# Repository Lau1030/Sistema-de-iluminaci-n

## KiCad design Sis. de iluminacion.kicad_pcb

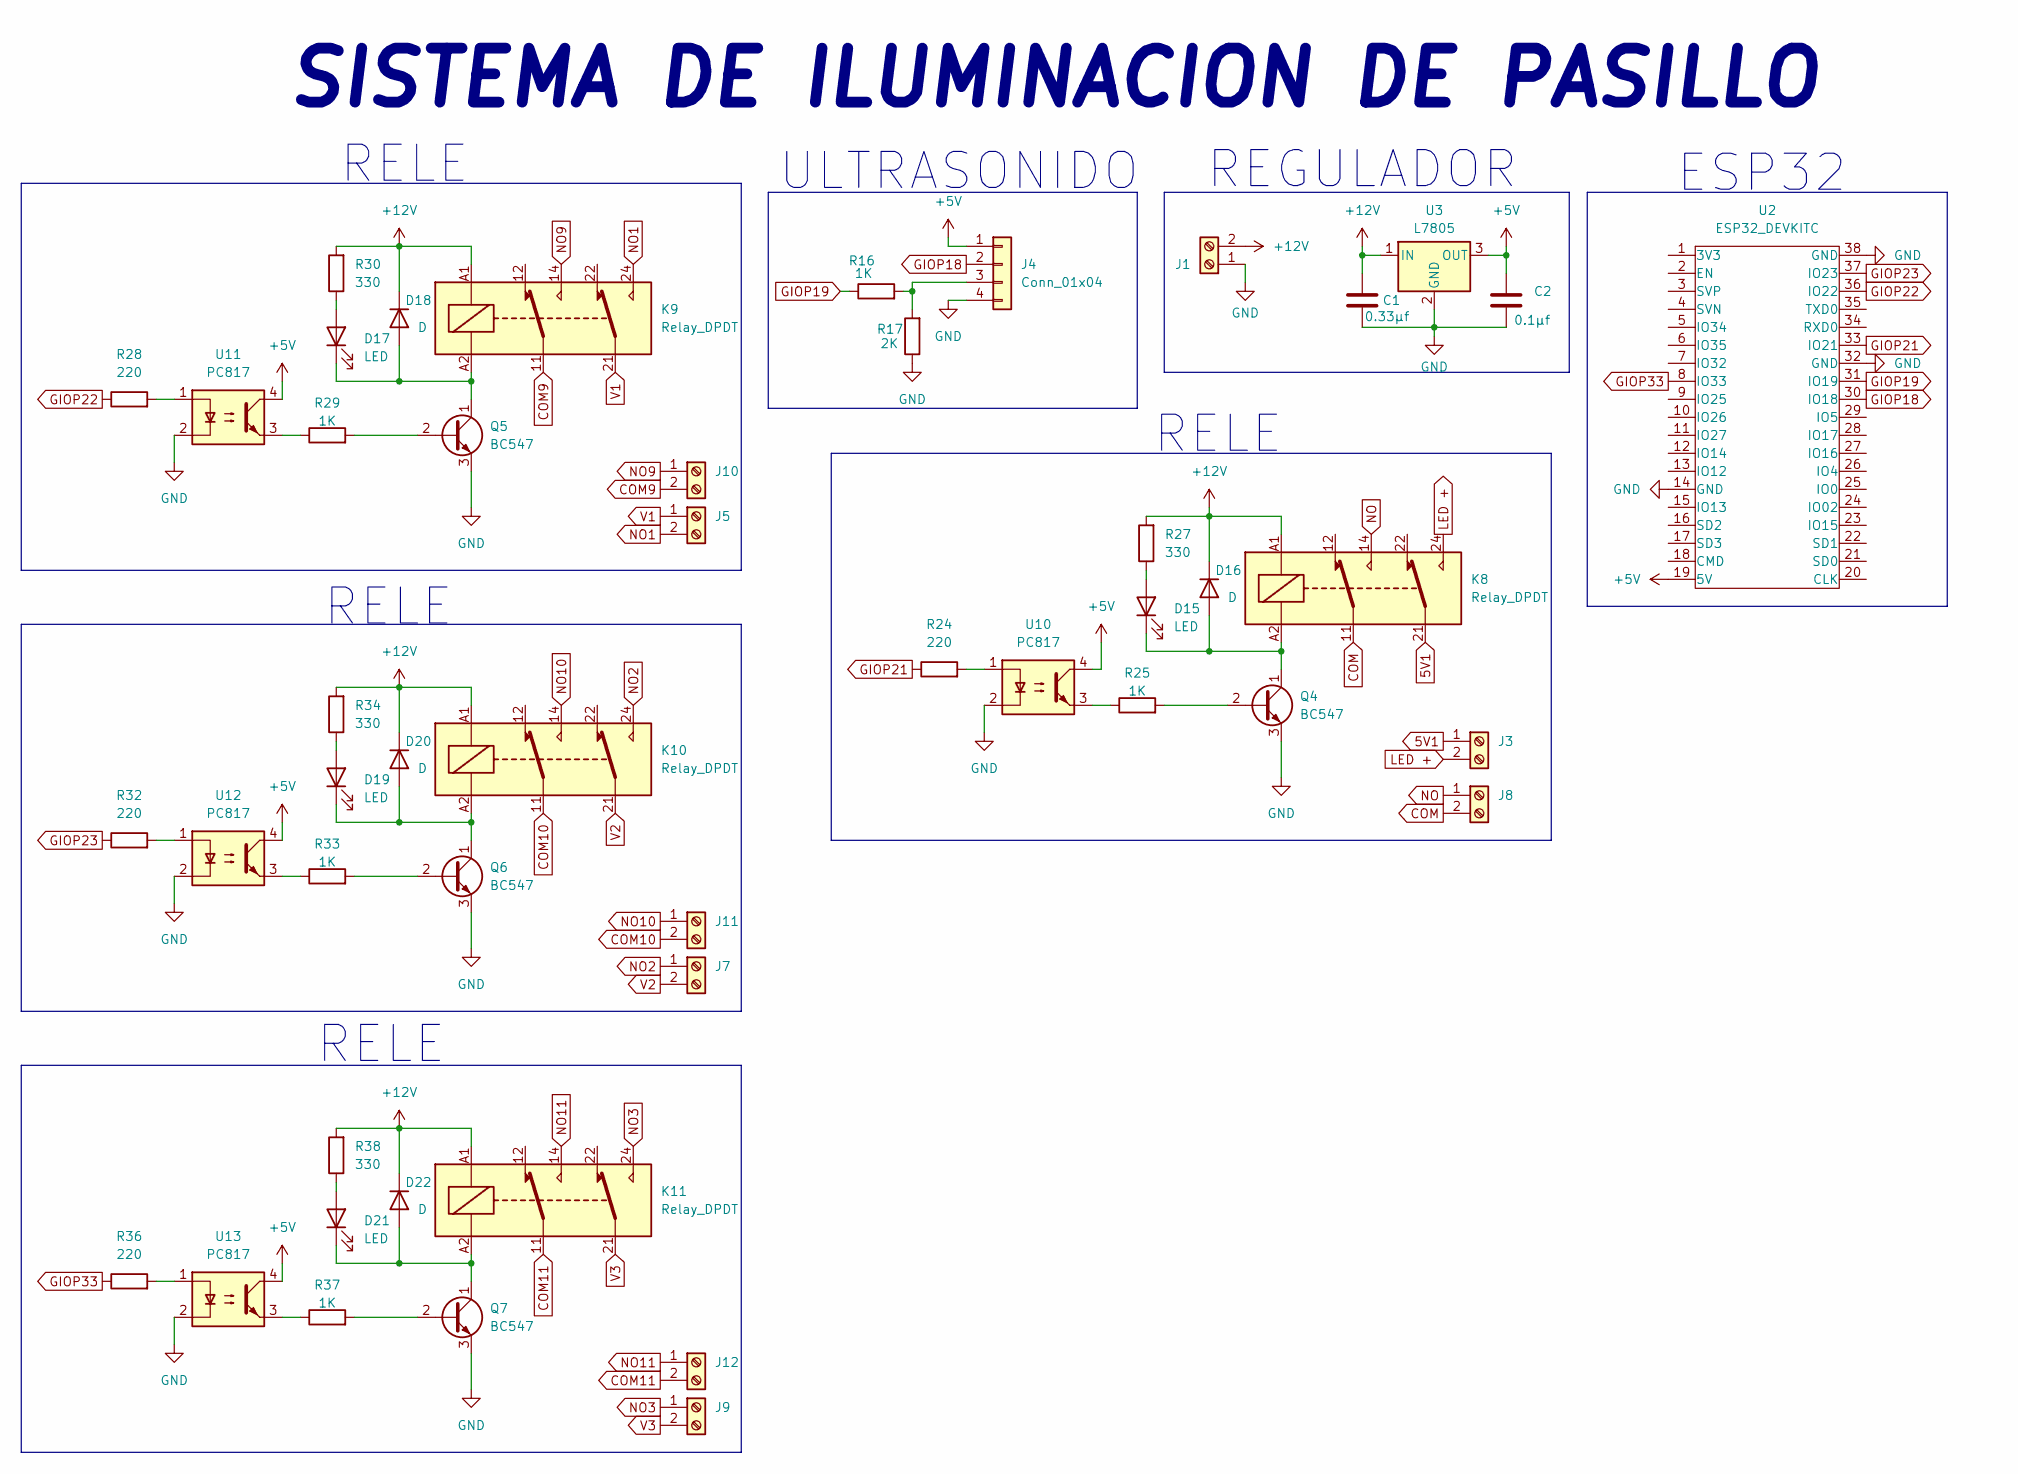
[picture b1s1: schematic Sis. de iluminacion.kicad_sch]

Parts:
C1: 0.33µf; C_0805_2012Metric
C2: 0.1µf; C_0805_2012Metric
D15, D17, D19, D21: LED; LED_0805_2012Metric
D16, D18, D20, D22: D; D_SMA
J1, J3, J5, J7, J8, J9, J10, J11, J12: Screw_Terminal_01x02; TerminalBlock_MaiXu_MX126-5.0-02P_1x02_P5.00mm
J4: Conn_01x04; PinSocket_1x04_P2.54mm_Vertical
K8, K9, K10, K11: Relay_DPDT; Relay_DPDT_Omron_G6A
Q4, Q5, Q6, Q7: BC547; TO-92_Wide
R16, R25, R29, R33, R37: 1K; R_0805_2012Metric
R17: 2K; R_0805_2012Metric
R24, R28, R32, R36: 220; R_0805_2012Metric
R27, R30, R34, R38: 330; R_0805_2012Metric
U2: ESP32_DEVKITC; ESP32S
U3: L7805; TO-263-3_TabPin2
U10, U11, U12, U13: PC817; DIP-4_W7.62mm

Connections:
5V1: J3.1, K8.21
+5V: C2.1, J4.1, U2.19 (5V), U3.3 (OUT), U10.4, U11.4, U12.4, U13.4
+12V: C1.1, D16.1 (K), D18.1 (K), D20.1 (K), D22.1 (K), J1.2, K8.A1, K9.A1, K10.A1, K11.A1, R27.2, R30.2, R34.2, R38.2, U3.1 (IN)
COM: J8.2, K8.11
COM9: J10.2, K9.11
COM10: J11.2, K10.11
COM11: J12.2, K11.11
GIOP18: J4.2, U2.30 (IO18)
GIOP19: R16.1, U2.31 (IO19)
GIOP21: R24.1, U2.33 (IO21)
GIOP22: R28.1, U2.36 (IO22)
GIOP23: R32.1, U2.37 (IO23)
GIOP33: R36.1, U2.8 (IO33)
GND: C1.2, C2.2, J1.1, J4.4, Q4.3 (E), Q5.3 (E), Q6.3 (E), Q7.3 (E), R17.1, U2.14 (GND), U2.32 (GND), U2.38 (GND), U3.2 (GND), U10.2, U11.2, U12.2, U13.2
LED +: J3.2, K8.24
NO: J8.1, K8.14
NO1: J5.2, K9.24
NO2: J7.1, K10.24
NO3: J9.1, K11.24
NO9: J10.1, K9.14
NO10: J11.1, K10.14
NO11: J12.1, K11.14
unnamed: D15.2 (A), R27.1
unnamed: D15.1 (K), D16.2 (A), K8.A2, Q4.1 (C)
unnamed: D17.2 (A), R30.1
unnamed: D17.1 (K), D18.2 (A), K9.A2, Q5.1 (C)
unnamed: D19.2 (A), R34.1
unnamed: D19.1 (K), D20.2 (A), K10.A2, Q6.1 (C)
unnamed: D21.2 (A), R38.1
unnamed: D21.1 (K), D22.2 (A), K11.A2, Q7.1 (C)
unnamed: J4.3, R16.2, R17.2
unnamed: Q4.2 (B), R25.2
unnamed: Q5.2 (B), R29.2
unnamed: Q6.2 (B), R33.2
unnamed: Q7.2 (B), R37.2
unnamed: R24.2, U10.1
unnamed: R25.1, U10.3
unnamed: R28.2, U11.1
unnamed: R29.1, U11.3
unnamed: R32.2, U12.1
unnamed: R33.1, U12.3
unnamed: R36.2, U13.1
unnamed: R37.1, U13.3
V1: J5.1, K9.21
V2: J7.2, K10.21
V3: J9.2, K11.21

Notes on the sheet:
RELE
SISTEMA DE ILUMINACION DE PASILLO
ULTRASONIDO
REGULADOR
ESP32

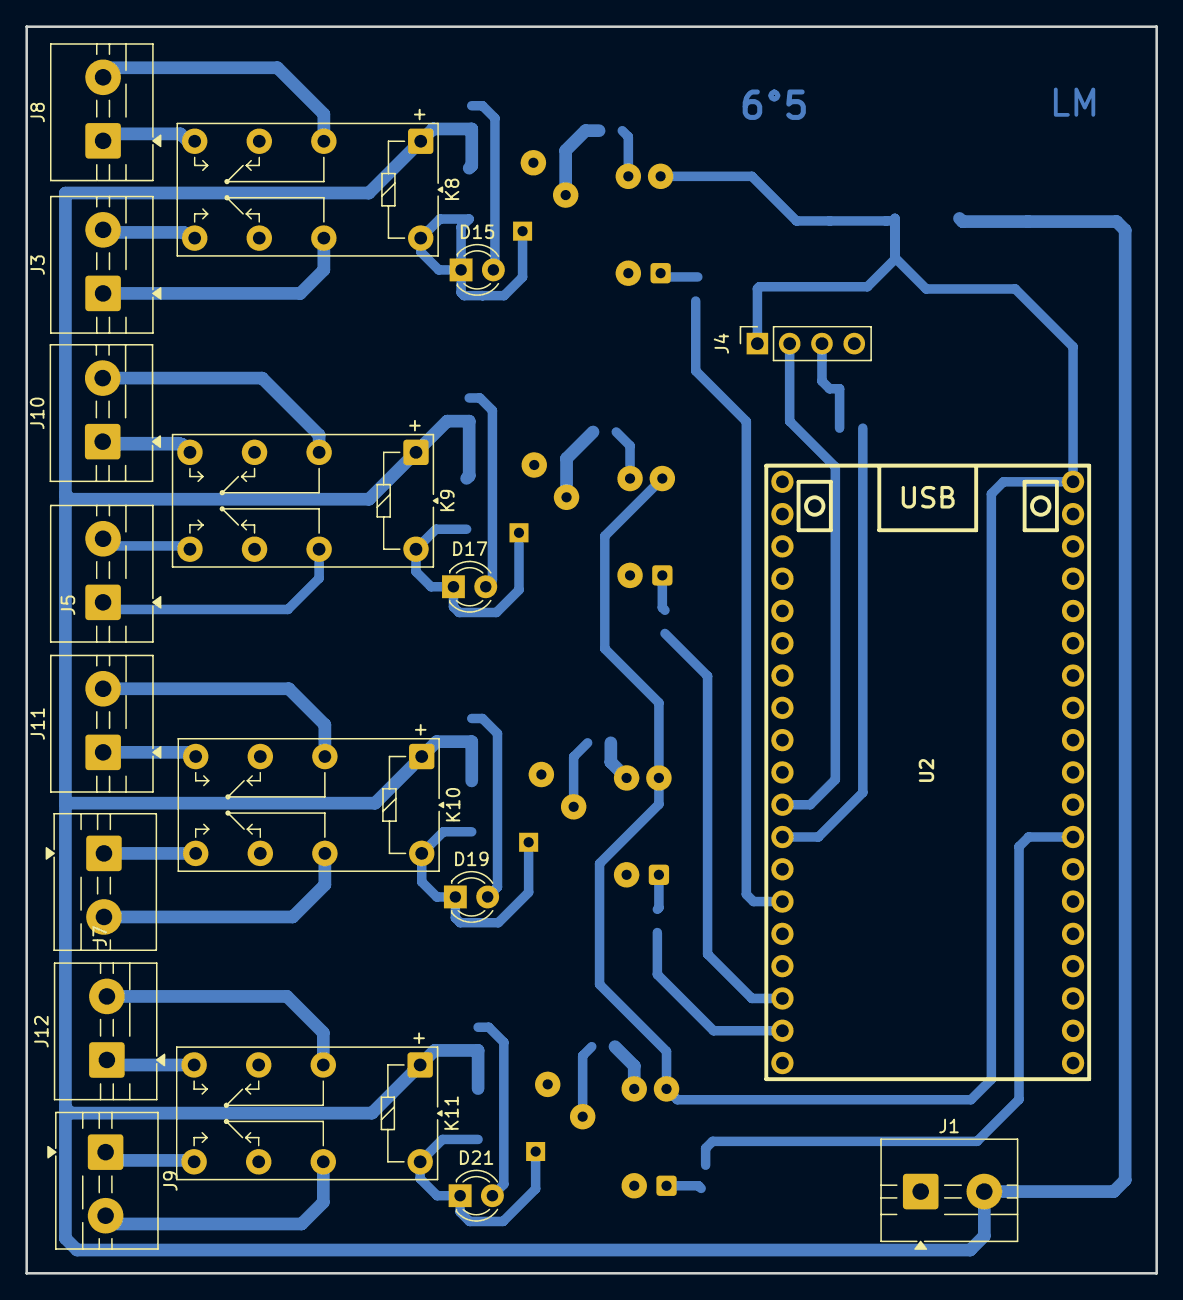
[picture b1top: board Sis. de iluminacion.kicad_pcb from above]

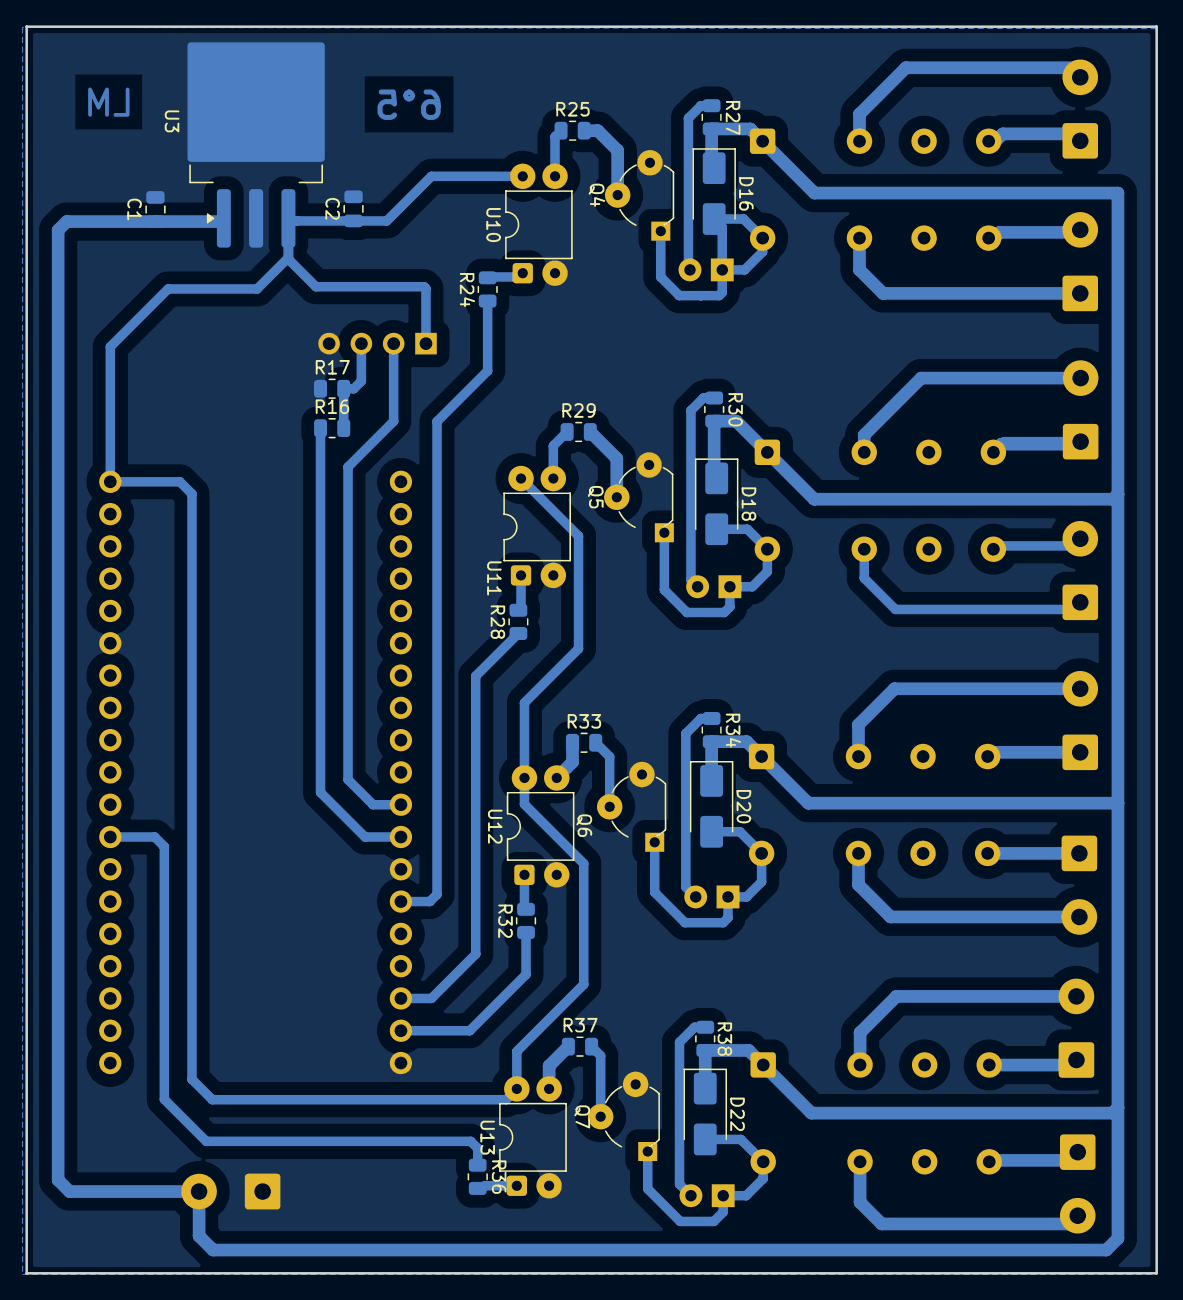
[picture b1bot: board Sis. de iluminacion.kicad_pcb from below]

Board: 2 copper layers, 88.9 x 98.1 mm, 48 parts (29 on the bottom side), 46 nets.

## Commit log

2025-05-25 Proyecto Rele
2025-06-07 Rele wifi
